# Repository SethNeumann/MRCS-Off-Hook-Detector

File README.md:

# REPO NAME: MRCS-Off-Hook-Detector
## License: Creative Commons Attribution-NonCommercial-ShareAlike

Provides a contact closure when phone goes off hook

intial version

The published project on the SPCoast.github.io website will
include the relevant git commit messages as a terse, high level
changelog, so don't replicate those messages here.

Many circuits used in telephony depend on knowing the state of a telephone station: whether it is on-hook or off-hook.  
Telephone people refer to this as “supervision” or in context of business telephone systems “A Lead Control.”  
In traditional office telephone systems, the “A lead” is grounded when the associated line appearance is in use.  
This ground is used to light a lamp and for control of the HOLD state.  
For model railroad telephone systems, the A lead is used to stop ringing or buzzing when a station is answered (goes off hook) 
and may be used for a busy station display where a LED or lamp lights when the associated phone is off-hook.  
Normally, when using classic telephones such as 500/554 desk and wall sets, we borrow one of the hook-switch contacts to provide an A lead.  
However not all telephones have an extra hook-switch contact, some consumer phones 
(including some retro decorator phones that have a nice transition-era look) are sealed and contacts are inaccessible 
and sometimes extra conductors are not available in the cable to the telephone.  
In those cases, it is useful to have a device which looks for current drawn on the telephone line itself and reports status accordingly 
(somewhat like a track occupancy detector).  This is the Off-Hook Detector.

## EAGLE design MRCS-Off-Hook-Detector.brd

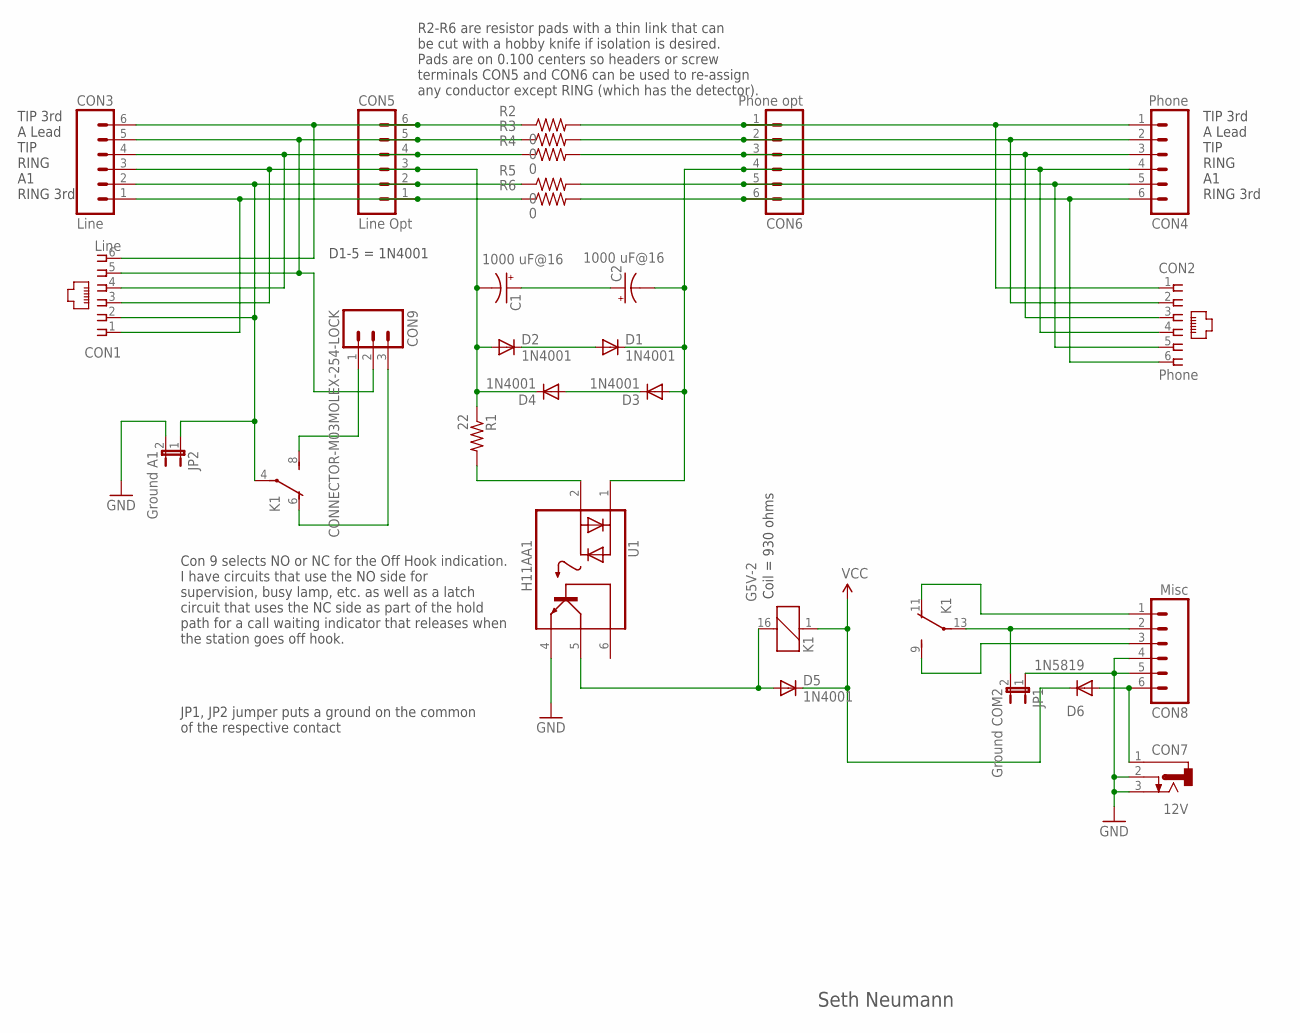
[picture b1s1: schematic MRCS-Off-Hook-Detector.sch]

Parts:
C1, C2: 1000 uF@16; E3,5-8
CON1: Line; RJ25-INVERTED
CON2: Phone; RJ25-INVERTED
CON3: Line; 1X06_LOCK
CON4: Phone; 1X06_LOCK
CON5: Line Opt; 1X06_LOCK
CON6: Phone opt; 1X06_LOCK
CON7: 12V; DCJ0202
CON8: Misc; 1X06_LOCK
CON9: CONNECTOR-M03MOLEX-254-LOCK; MOLEX-1X3_LOCK
D1, D2, D3, D4, D5: 1N4001; DIODE-1N4001
D6: 1N5819; DIODE-1N4001
JP1: Ground COM2; 1X02
JP2: Ground A1; 1X02
K1: G5V-2
R1: 22; AXIAL-0.4-RES
R2, R3, R4, R5, R6: 0; CUT-R
U1: H11AA1; DIP762W50P254L730H410Q6

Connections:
3RL: CON1.1, CON3.1, CON5.1, R6.P2 (1)
3RS: CON2.6, CON4.6, CON6.6, R6.P1 (2)
3TL: CON1.6, CON3.6, CON5.6, R2.P2 (1)
3TS: CON2.1, CON4.1, CON6.1, R2.P1 (2)
+12: CON7.1, CON8.6, D6.A
A1_LINE: CON1.2, CON3.2, CON5.2, JP2.1, K1.4, R5.P2 (1)
A1_PHONE: CON2.5, CON4.5, CON6.5, R5.P1 (2)
A_LINE: CON1.5, CON3.5, CON5.5, CON9.2, R3.P2 (1)
A_PHONE: CON2.2, CON4.2, CON6.2, R3.P1 (2)
GND: CON7.2, CON7.3, CON8.4, CON8.5, JP1.1, JP2.2, U1.4 (E)
unnamed: D5.A, K1.16 (2), U1.5 (C)
unnamed: R1.P$2 (2), U1.2 (C/A)
unnamed: CON8.1, K1.11 (O)
unnamed: D1.A, D2.C
unnamed: C1.+, C2.+
unnamed: D3.C, D4.A
unnamed: CON9.1, K1.8 (S)
unnamed: CON9.3, K1.6 (O)
unnamed: CON8.2, JP1.2, K1.13
unnamed: CON8.3, K1.9 (S)
RING-PHONE: C2.-, CON2.4, CON4.4, CON6.4, D1.C, D3.A, U1.1 (A/C)
RING_LINE: C1.-, CON1.3, CON3.3, CON5.3, D2.A, D4.C, R1.P$1 (1)
TIP_LINE: CON1.4, CON3.4, CON5.4, R4.P2 (1)
TIP_PHONE: CON2.3, CON4.3, CON6.3, R4.P1 (2)
VCC: D5.C, D6.C, K1.1

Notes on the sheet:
D1-5 = 1N4001
Coil = 930 ohms
Con 9 selects NO or NC for the Off Hook indication. I have circuits that use the NO side for supervision, busy lamp, etc. as well as a latch circuit that uses the NC side as part of the hold path for a call waiting indicator that releases when the station goes off hook.
R2-R6 are resistor pads with a thin link that can be cut with a hobby knife if isolation is desired. Pads are on 0.100 centers so headers or screw terminals CON5 and CON6 can be used to re-assign any conductor except RING (which has the detector).
JP1, JP2 jumper puts a ground on the common of the respective contact
TIP 3rd A Lead TIP RING A1 RING 3rd
Seth Neumann

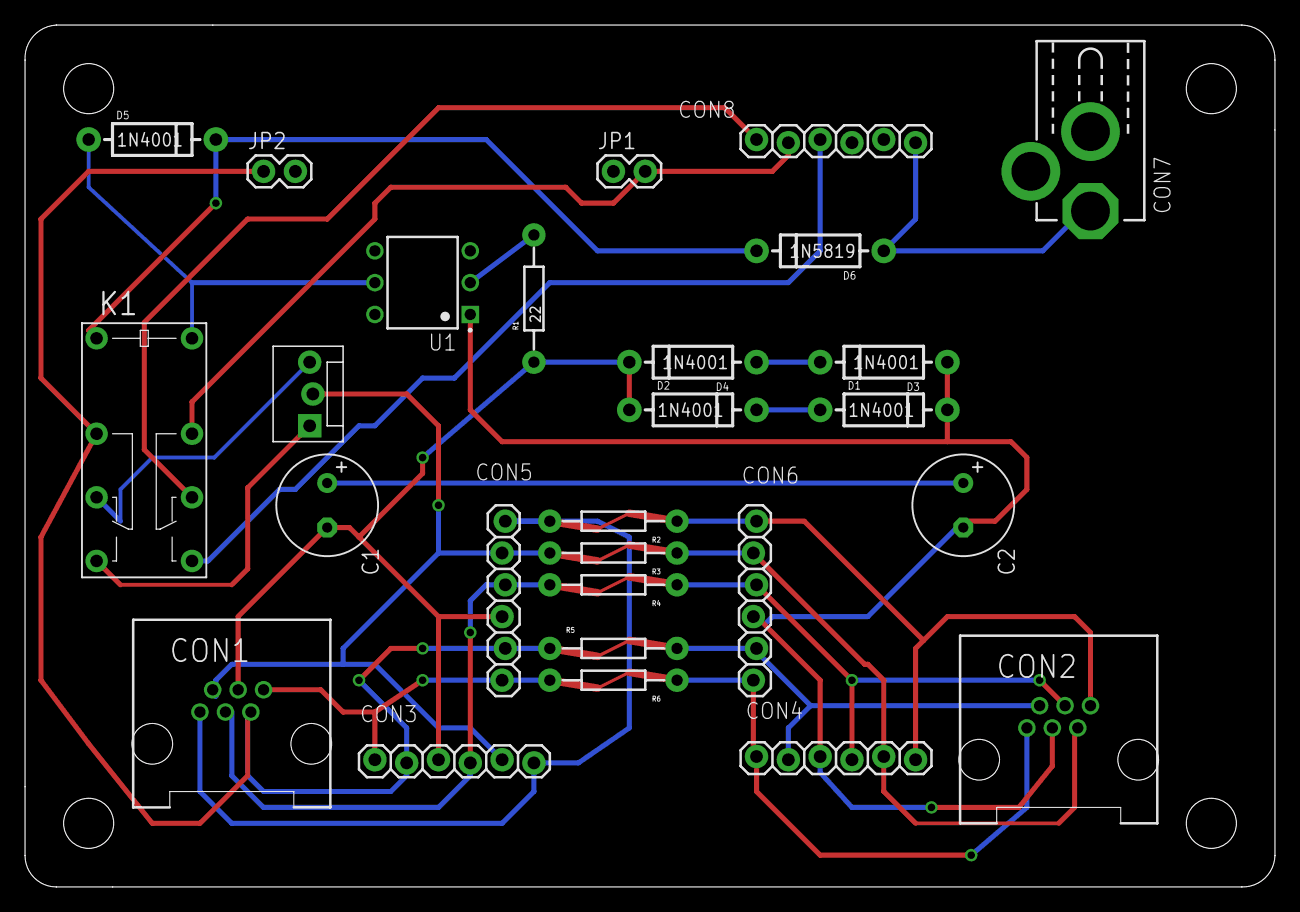
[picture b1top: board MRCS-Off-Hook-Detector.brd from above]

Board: 2 copper layers, 99.8 x 68.8 mm, 32 parts (0 on the bottom side), 25 nets.

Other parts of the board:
U$1: BOARD-DINRAIL-2.7IN
U$2: CA-PROP65WARNING
U$3: MRCSLOGOBTM
U$4, U$5: MRCSLOGOTOP

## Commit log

2020-07-30 git hub setting up
2020-07-30 copying new files from old directory
2020-07-30 added instructions
2020-07-31 add BOM to git

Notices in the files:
parts and their libraries:
SparkFun-Aesthetics: Licensing: CC v3.0 Share-Alike You are welcome to use this library for commercial purposes.
